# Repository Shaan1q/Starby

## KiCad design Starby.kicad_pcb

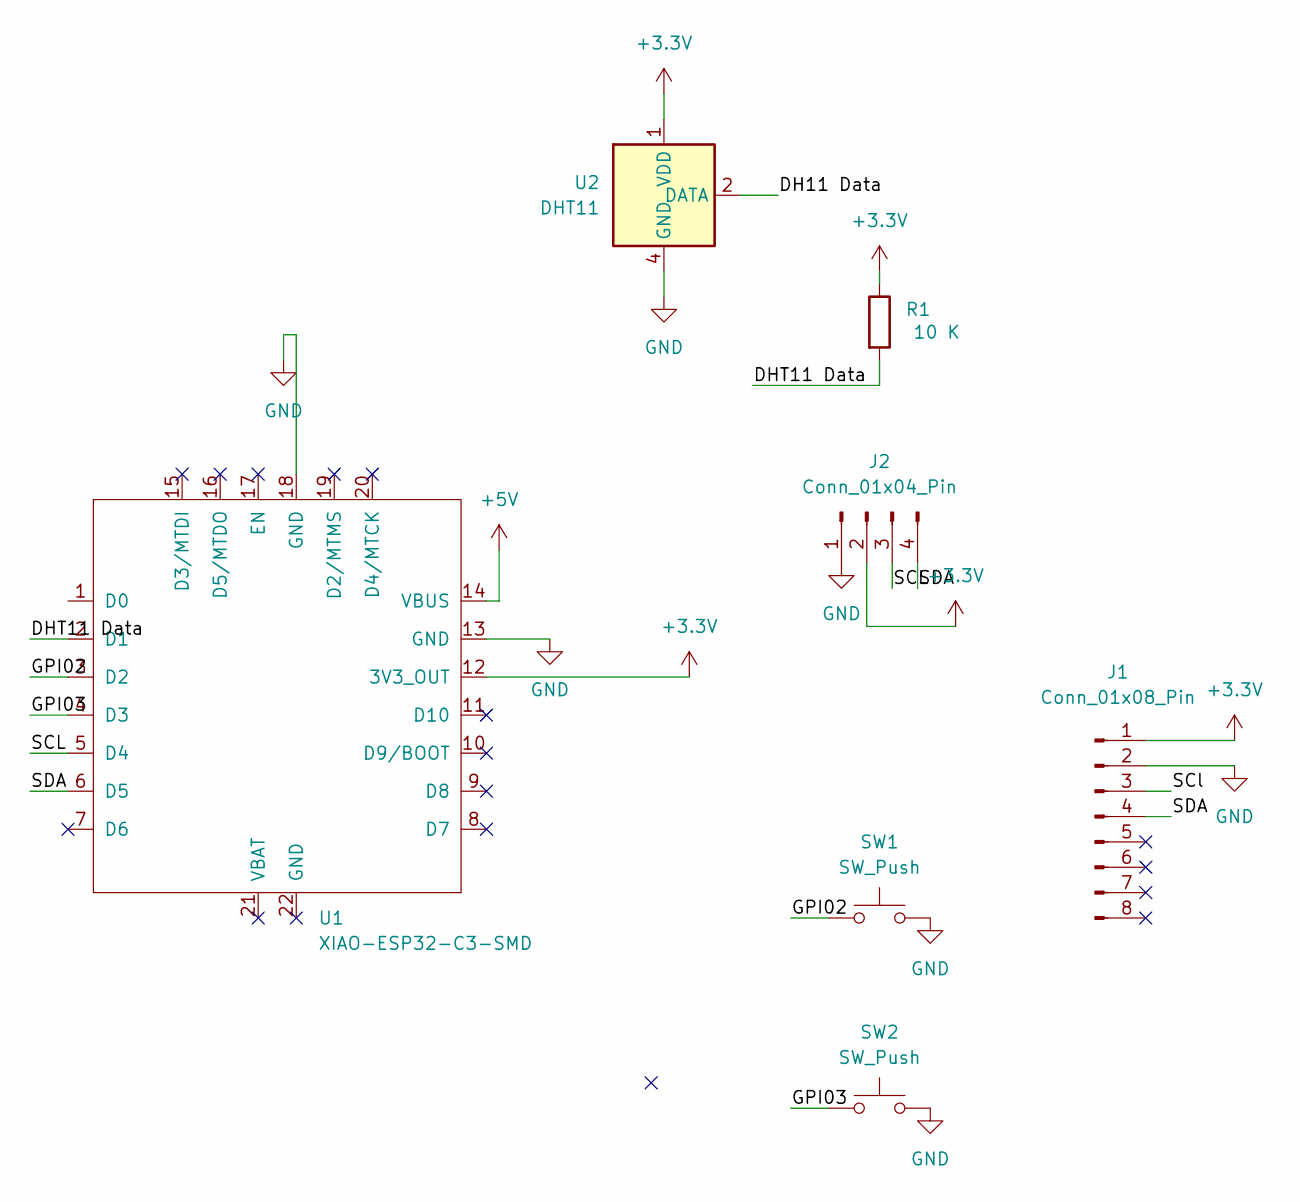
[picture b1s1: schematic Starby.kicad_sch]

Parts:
J1: Conn_01x08_Pin; PinHeader_1x08_P2.54mm_Vertical
J2: Conn_01x04_Pin; Display_128x64_096_I2C
R1: 10 K; R_Axial_DIN0204_L3.6mm_D1.6mm_P7.62mm_Horizontal
SW1, SW2: SW_Push; SW_Cherry_MX_1.00u_PCB
U1: XIAO-ESP32-C3-SMD
U2: DHT11; Aosong_DHT11_5.5x12.0_P2.54mm

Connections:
+3.3V: J1.1, J2.2, R1.1, U1.12 (3V3_OUT), U2.1 (VDD)
+5V: U1.14 (VBUS)
/DH11 Data: U2.2 (DATA)
/DHT11 Data: R1.2, U1.2 (D1)
/GPI02: SW1.1, U1.3 (D2)
/GPI03: SW2.1, U1.4 (D3)
/SCL: J2.3, U1.5 (D4)
/SCl: J1.3
/SDA: J1.4, J2.4, U1.6 (D5)
GND: J1.2, J2.1, SW1.2, SW2.2, U1.13 (GND), U1.18 (GND), U2.4 (GND)

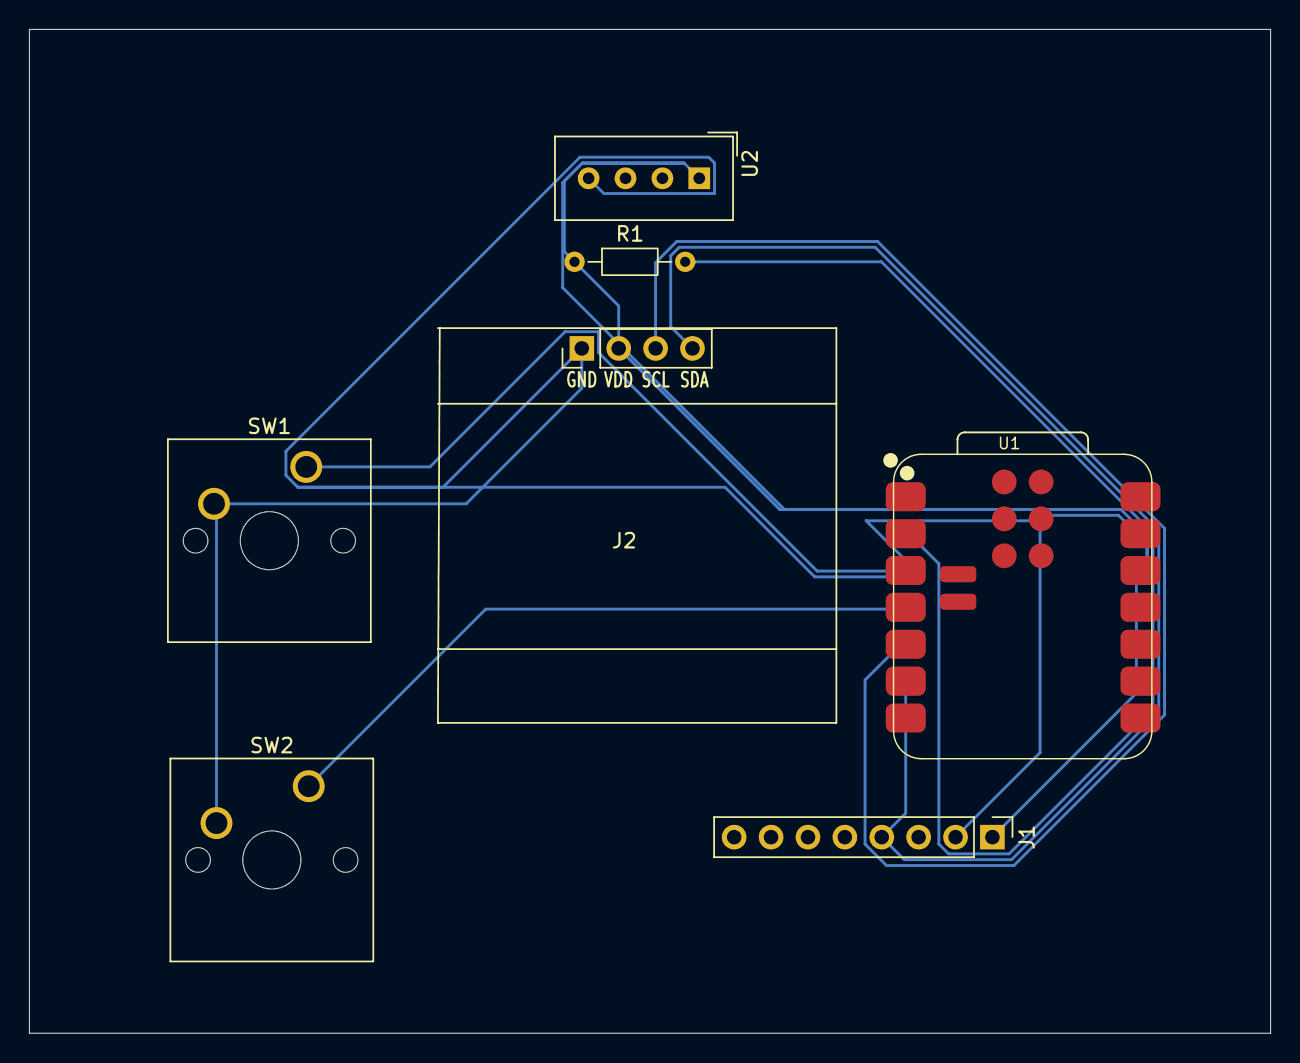
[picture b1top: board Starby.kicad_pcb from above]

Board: 2 copper layers, 85.5 x 69.1 mm, 7 parts (0 on the bottom side), 7 nets.
